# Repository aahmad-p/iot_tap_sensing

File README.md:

# _flomon_: A Water Tap Monitoring IoT System
This repository contains code and CAD (electrical and mechanical) files for _flomon_. This is a brief summary of the contents (by folder):
- ECAD: Contains electrical schematic and PCB layout files for custom sensor module (utilizing nRF52805 SoC for Bluetooth connectivity).
- Firmware: Contains firmware for sensor module (written in _C_).
- Gateway: Contains code for gateway (Raspberry Pi) interfacing with AWS IoT Core (written in _python_) .
- MCAD: Contains mechanical drawings for custom gateway and sensor housings (including custom adapter fittings).

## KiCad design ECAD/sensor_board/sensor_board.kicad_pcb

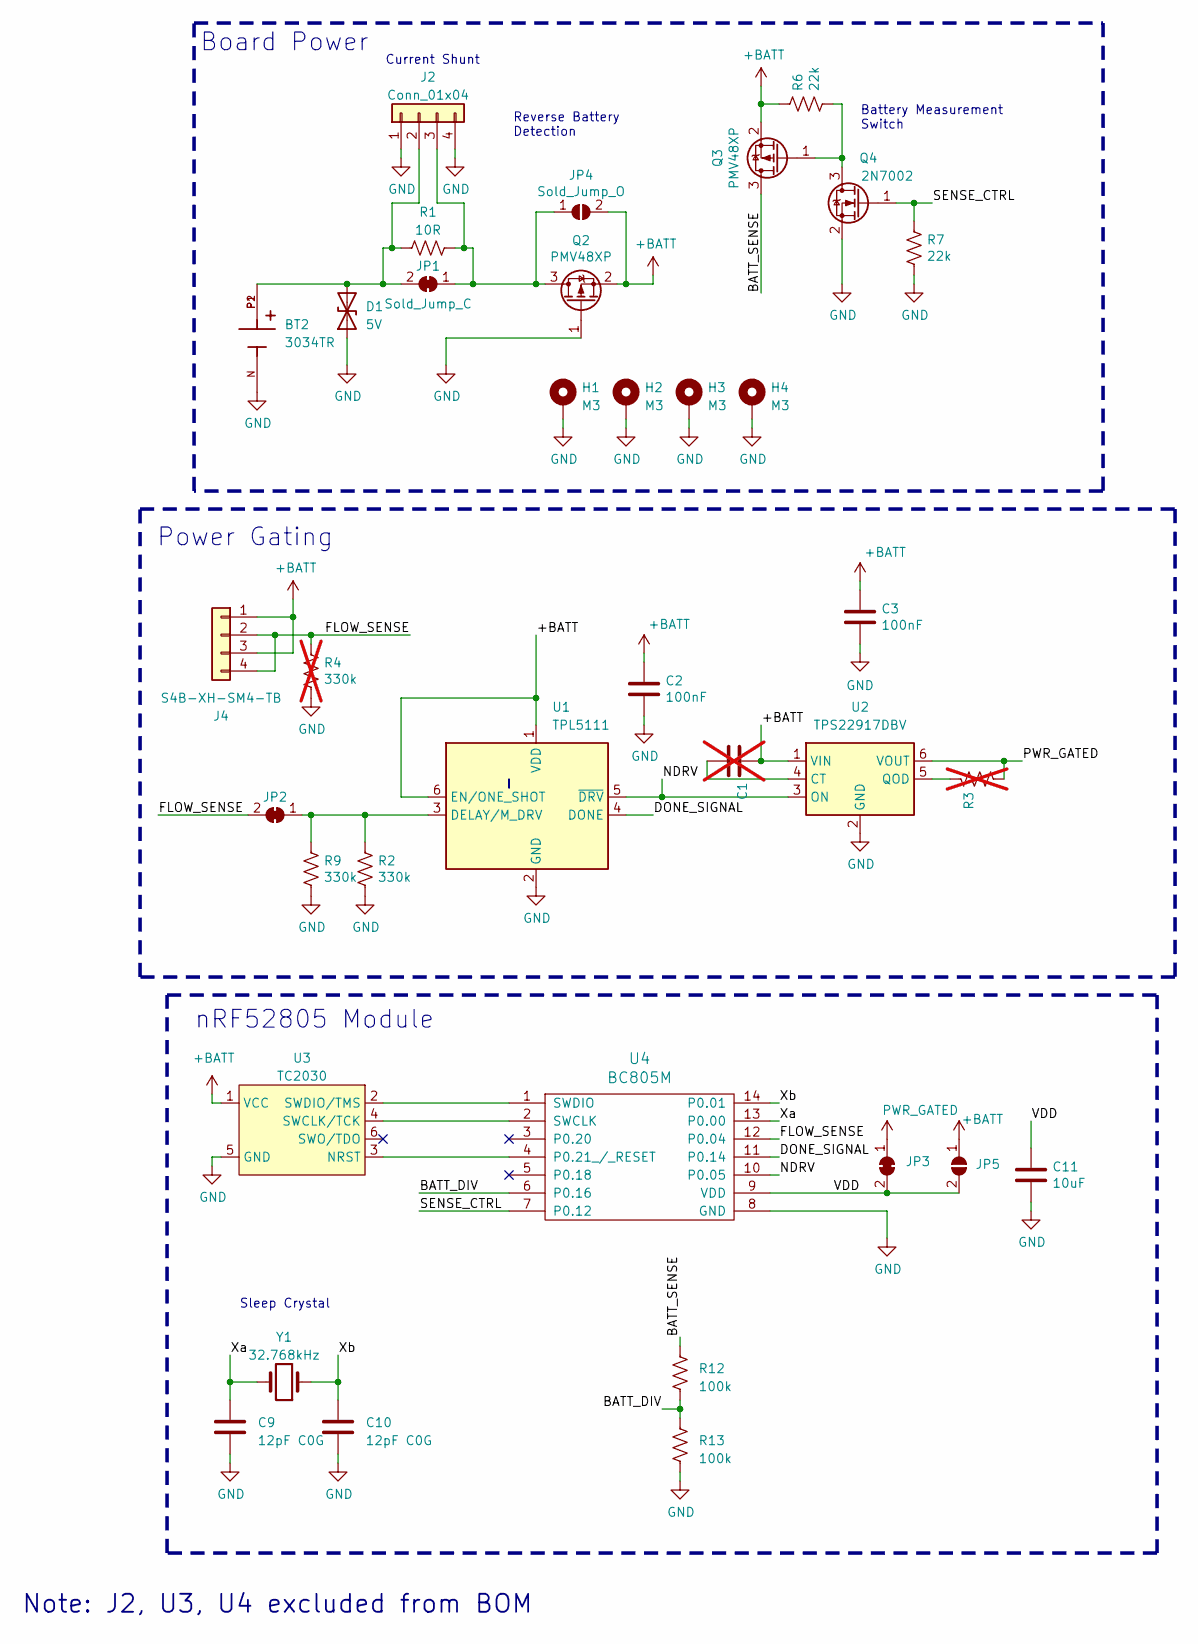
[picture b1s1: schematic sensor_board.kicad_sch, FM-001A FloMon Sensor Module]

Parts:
BT2: 3034TR; BAT_3034TR; PARTREV E; JLC C5213768
C1: C_0603_1608Metric; not fitted
C2, C3: 100nF; C_0603_1608Metric; MPN CC0603KRX7R9BB104; JLC C14663
C9, C10: 12pF C0G; C_0402_1005Metric; MPN 0402CG120J500NT; JLC C1547
C11: 10uF; C_0805_2012Metric; MPN CL21A106KAYNNNE; JLC C15850
D1: 5V; D_SOD-323; MPN PESD5V0V1BA,115; JLC C552583
H1, H2, H3, H4: M3; MountingHole_2.2mm_M2_Pad
J2: Conn_01x04; Test_Wire_Pad_x4
J4: S4B-XH-SM4-TB; CONN4_S4B-XH_JST; JLC C161861
JP1: Sold_Jump_C; SolderJumper-2_P1.3mm_Bridged_RoundedPad1.0x1.5mm
JP2, JP3: SolderJumper-2_P1.3mm_Bridged_RoundedPad1.0x1.5mm
JP4: Sold_Jump_O; SolderJumper-2_P1.3mm_Open_RoundedPad1.0x1.5mm
JP5: SolderJumper-2_P1.3mm_Open_RoundedPad1.0x1.5mm
Q2, Q3: PMV48XP; SOT-23; MPN PMV48XP; JLC C2959854
Q4: 2N7002; SOT-23; JLC C916396
R1: 10R; R_0603_1608Metric; MPN 0603WAF100JT5E; JLC C22859
R2, R9: 330k; R_0603_1608Metric; MPN CR0603FA3303G; JLC C100970
R3: R_0603_1608Metric; not fitted
R4: 330k; R_0603_1608Metric; MPN CR0603FA3303G; JLC C100970; not fitted
R6, R7: 22k; R_0603_1608Metric; MPN 0603WAF2202T5E; JLC C31850
R12, R13: 100k; R_0603_1608Metric; MPN 0603WAF1003T5E; JLC C25803
U1: TPL5111; SOT-23-6; JLC C2870554
U2: TPS22917DBV; SOT-23-6; JLC C2681320
U3: TC2030; TC2030-IDC-NL
U4: BC805M; BC805M_No_Paste
Y1: 32.768kHz; Crystal_SMD_3215-2Pin_3.2x1.5mm; MPN Q13FC1350000400; JLC C32346

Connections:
+BATT: C1.1, C2.1, C3.1, J4.1, J4.3, JP4.2 (B), JP5.1 (A), Q2.2 (S), Q3.2 (S), R6.1, U1.1 (VDD), U1.6 (EN/ONE_SHOT), U2.1 (VIN), U3.1 (VCC)
/BATT_DIV: R12.2, R13.1, U4.6 (P0.16)
/BATT_SENSE: Q3.3 (D), R12.1
/DONE_SIGNAL: U1.4 (DONE), U4.11 (P0.14)
/FLOW_SENSE: J4.2, J4.4, JP2.2 (B), R4.1, U4.12 (P0.04)
/NDRV: U1.5 (~DRV), U2.3 (ON), U4.10 (P0.05)
/SENSE_CTRL: Q4.1 (G), R7.1, U4.7 (P0.12)
/VDD: C11.1, JP3.2 (B), JP5.2 (B), U4.9 (VDD)
/Xa: C9.2, U4.13 (P0.00), Y1.2
/Xb: C10.2, U4.14 (P0.01), Y1.1
GND: BT2.N, C2.2, C3.2, C9.1, C10.1, C11.2, D1.1 (A1), H1.1, H2.1, H3.1, H4.1, J2.1, J2.4, Q2.1 (G), Q4.2 (S), R2.2, R4.2, R7.2, R9.2, R13.2, U1.2 (GND), U2.2 (GND), U3.5 (GND), U4.8 (GND)
unnamed: BT2.P1, BT2.P2, D1.2 (A2), J2.2, JP1.2 (B), R1.1
unnamed: J2.3, JP1.1 (A), JP4.1 (A), Q2.3 (D), R1.2
unnamed: JP2.1 (A), R2.1, R9.1, U1.3 (DELAY/M_DRV)
unnamed: Q3.1 (G), Q4.3 (D), R6.2
unnamed: C1.2, U2.4 (CT)
unnamed: R3.1, U2.5 (QOD)
unnamed: U3.3 (NRST), U4.4 (P0.21_/_RESET)
unnamed: U3.4 (SWCLK/TCK), U4.2 (SWCLK)
unnamed: U3.2 (SWDIO/TMS), U4.1 (SWDIO)
PWR_GATED: JP3.1 (A), R3.2, U2.6 (VOUT)

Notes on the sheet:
Power Gating
Battery Measurement Switch
Sleep Crystal
Note: J2, U3, U4 excluded from BOM
Current Shunt
Board Power
Reverse Battery Detection
nRF52805 Module

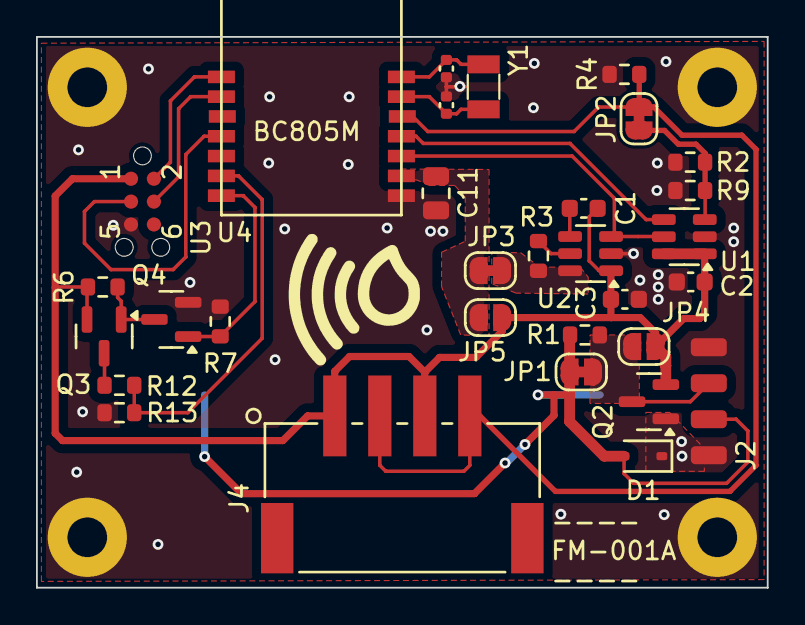
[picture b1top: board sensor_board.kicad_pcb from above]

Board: 2 copper layers, 40.6 x 30.6 mm, 36 parts (1 on the bottom side), 21 nets.

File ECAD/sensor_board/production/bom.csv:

Comment,Designator,Footprint,LCSC Part Number
12pF C0G,"C10, C9",402,C1547
10uF,C11,805,C15850
100nF,"C2, C3",603,C14663
5V,D1,D_SOD-323,C552583
S4B-XH-SM4-TB,J4,CONN4_S4B-XH_JST,C161861
PMV48XP,"Q2, Q3",SOT-23,C2959854
2N7002,Q4,SOT-23,C916396
10R,R1,603,C22859
100k,"R12, R13",603,C25803
330k,"R2, R9",603,C100970
22k,"R6, R7",603,C31850
TPL5111,U1,SOT-23-6,C2870554
TPS22917DBV,U2,SOT-23-6,C2681320
32.768kHz,Y1,Crystal_SMD_3215-2Pin_3.2x1.5mm,C32346

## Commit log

2024-11-02 Adding schematic starting point for sensor
2024-11-06 Pushing sensor board schematic (in progress)
2024-11-06 Pushing updates to schematic
2024-11-07 Format and adding footprints
2024-11-07 PCB Editor updates: updated settings (e.g. Design Rules under Board Setup), added footprints to library, added parts to PCB
2024-11-11 Initial version of routed board
2024-11-12 Updated board layout
2024-11-12 Additional minor changes to layout
2024-11-13 Pushing completed layout
2024-11-21 Adding prototype BLE adv recieving code
2024-11-21 Pushing production files and other changes (board has arrived)
2024-11-29 Adding firmware
2024-12-03 Final gateway code
2024-12-03 Adding CAD outputs
2024-12-04 Removed old ECAD project files
2024-12-12 Adding XTAL datasheet and 3D model
